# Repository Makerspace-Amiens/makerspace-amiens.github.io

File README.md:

# Makerspace UniLaSalle Amiens

Site vitrine du Makerspace d'UniLaSalle Amiens : <https://makerspace-amiens.fr>

Le site est une page unique et autonome (`index.html`) : toutes les ressources (scripts, modèle 3D, polices) y sont intégrées. Elle est déployée sur GitHub Pages par le workflow `.github/workflows/pages.yml` à chaque push sur `main`.

## Ancien site

L'ancien site Jekyll est archivé :

- branche [`archive`](../../tree/archive)
- tag `site-v1-archive`

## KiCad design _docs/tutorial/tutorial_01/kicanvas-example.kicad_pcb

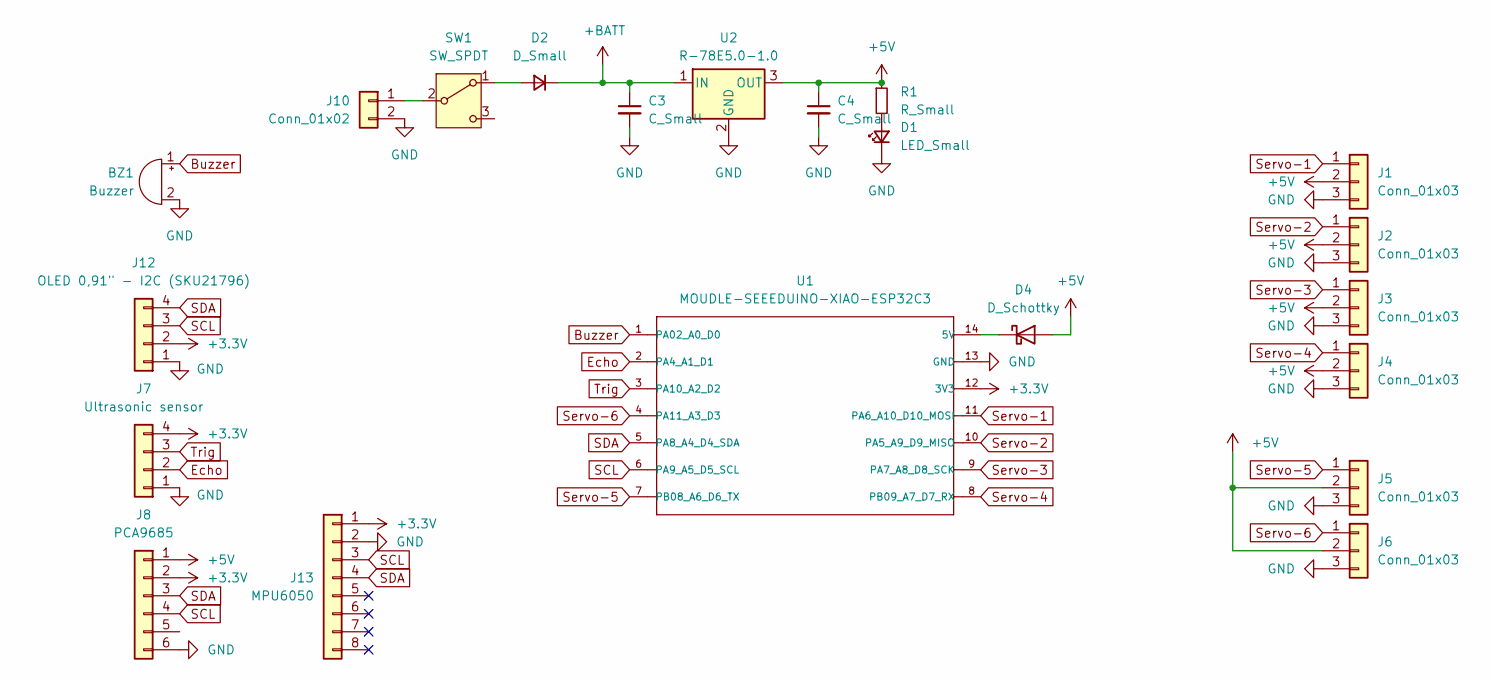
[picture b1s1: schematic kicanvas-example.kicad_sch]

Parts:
BZ1: Buzzer; Buzzer_12x9.5RM7.6
C3, C4: C_Small; C_Disc_D6.0mm_W2.5mm_P5.00mm
D1: LED_Small; LED_D5.0mm
D2: D_Small; D_A-405_P7.62mm_Horizontal
D4: D_Schottky; D_A-405_P7.62mm_Horizontal
J1, J2, J3, J4, J5, J6: Conn_01x03; PinHeader_1x03_P2.54mm_Vertical
J7: Ultrasonic sensor; PinSocket_1x04_P2.54mm_Vertical
J8: PCA9685; PinSocket_1x06_P2.54mm_Vertical
J10: Conn_01x02; Molex_KK-254_AE-6410-02A_1x02_P2.54mm_Vertical
J12: OLED 0,91" - I2C (SKU21796); PinSocket_1x04_P2.54mm_Vertical
J13: MPU6050; PinSocket_1x08_P2.54mm_Vertical
R1: R_Small; R_Axial_DIN0207_L6.3mm_D2.5mm_P10.16mm_Horizontal
SW1: SW_SPDT; SW_100SP1T1B4M2QE
U1: MOUDLE-SEEEDUINO-XIAO-ESP32C3; MOUDLE14P-SMD-2.54-21X17.8MM
U2: R-78E5.0-1.0; Converter_DCDC_RECOM_R-78E-0.5_THT

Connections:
+3.3V: J7.4, J8.2, J12.2, J13.1, U1.12 (3V3)
+5V: C4.1, D4.2 (A), J1.2, J2.2, J3.2, J4.2, J5.2, J6.2, J8.1, R1.1, U2.3 (OUT)
+BATT: C3.1, D2.1 (K), U2.1 (IN)
Buzzer: BZ1.1 (+), U1.1 (PA02_A0_D0)
EN-Driver: J6.1, U1.4 (PA11_A3_D3)
Echo: J7.2, U1.2 (PA4_A1_D1)
GND: BZ1.2 (-), C3.2, C4.2, D1.1 (K), J1.3, J2.3, J3.3, J4.3, J5.3, J6.3, J7.1, J8.6, J10.2, J12.1, J13.2, U1.13 (GND), U2.2 (GND)
unnamed: D1.2 (A), R1.2
unnamed: D2.2 (A), SW1.1 (A)
unnamed: D4.1 (K), U1.14 (5V)
unnamed: J10.1, SW1.2 (B)
SCL: J8.4, J12.3, J13.3, U1.6 (PA9_A5_D5_SCL)
SDA: J8.3, J12.4, J13.4, U1.5 (PA8_A4_D4_SDA)
Servo-1: J1.1, U1.11 (PA6_A10_D10_MOSI)
Servo-2: J2.1, U1.10 (PA5_A9_D9_MISO)
Servo-3: J3.1, U1.9 (PA7_A8_D8_SCK)
Servo-4: J4.1, U1.8 (PB09_A7_D7_RX)
Servo-5: J5.1, U1.7 (PB08_A6_D6_TX)
Trig: J7.3, U1.3 (PA10_A2_D2)

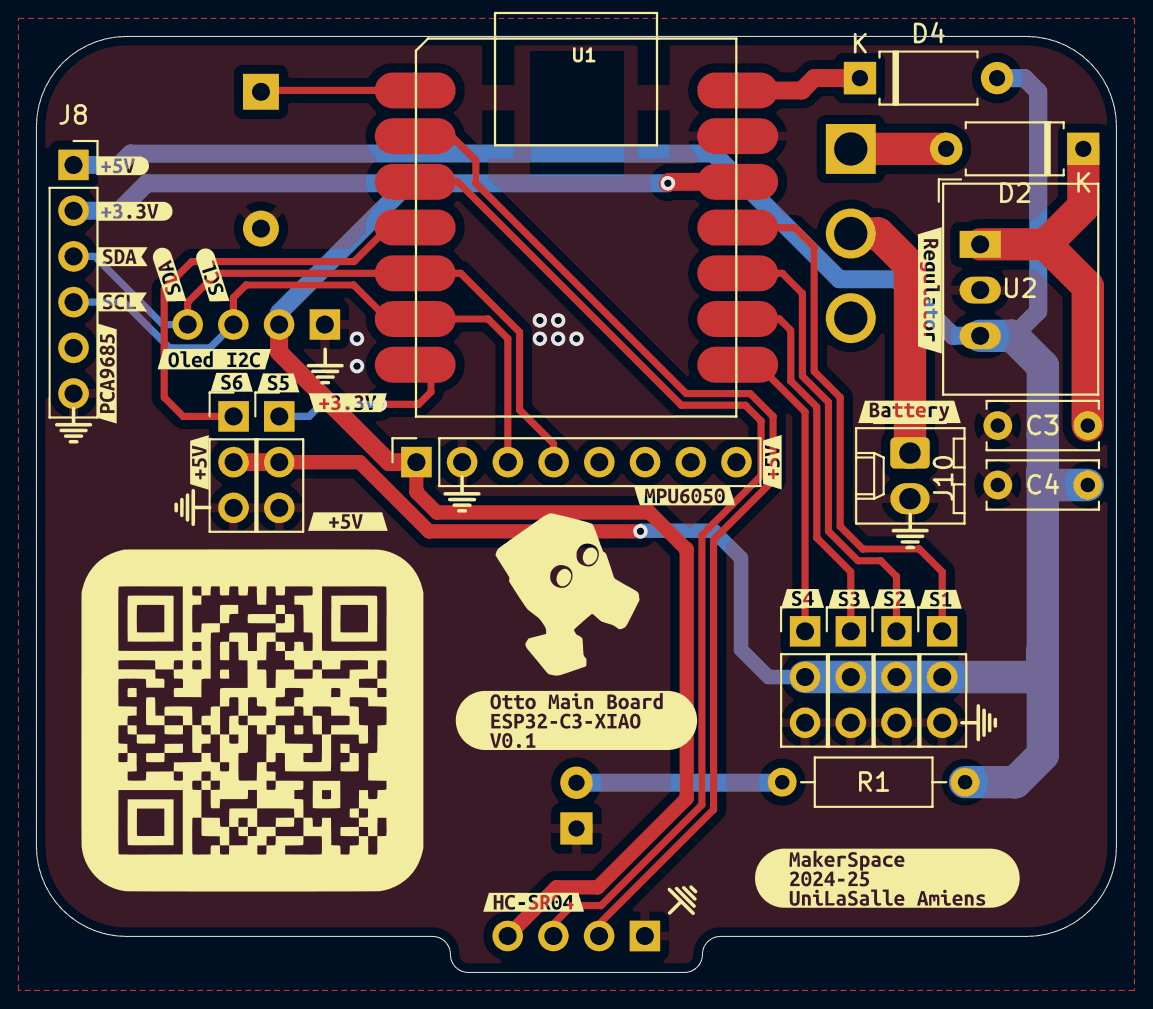
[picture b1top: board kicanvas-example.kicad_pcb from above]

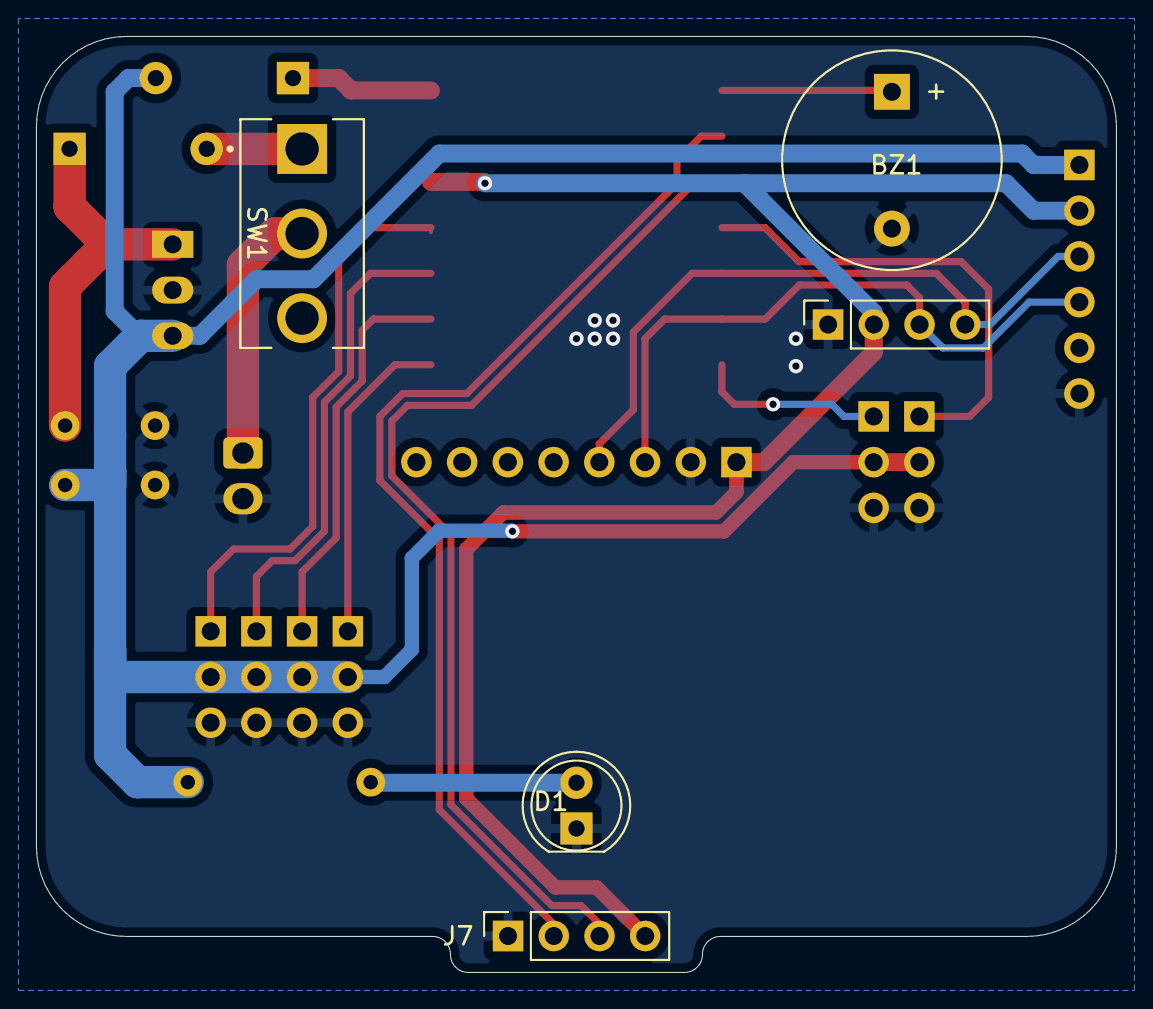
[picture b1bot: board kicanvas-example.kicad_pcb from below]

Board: 2 copper layers, 60.0 x 52.0 mm, 45 parts (5 on the bottom side), 19 nets.

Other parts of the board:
kibuzzard-66E45A06: G***; kibuzzard-66E45A06
kibuzzard-66E45A30: G***; kibuzzard-66E45A30
kibuzzard-66E45AAF: G***; kibuzzard-66E45AAF
kibuzzard-66E45B4D: G***; kibuzzard-66E45B4D
kibuzzard-66E45B8A: G***; kibuzzard-66E45B8A
kibuzzard-66E45B15, kibuzzard-66E45B15#2: G***; kibuzzard-66E45B15
kibuzzard-66E45B34: G***; kibuzzard-66E45B34
kibuzzard-66E45B47: G***; kibuzzard-66E45B47
kibuzzard-66E45B51: G***; kibuzzard-66E45B51
kibuzzard-66E45B85: G***; kibuzzard-66E45B85
kibuzzard-66E45BAB: G***; kibuzzard-66E45BAB
kibuzzard-66E45BBF: G***; kibuzzard-66E45BBF
kibuzzard-66E45BE1: G***; kibuzzard-66E45BE1
kibuzzard-66E45BF0: G***; kibuzzard-66E45BF0
kibuzzard-66E45C9B: G***; kibuzzard-66E45C9B
kibuzzard-66E45C62: G***; kibuzzard-66E45C62
kibuzzard-66E460A4: G***; kibuzzard-66E460A4
kibuzzard-66E460BA: G***; kibuzzard-66E460BA
kibuzzard-66E460D9: G***; kibuzzard-66E460D9
kibuzzard-66E46157: G***; kibuzzard-66E46157
kibuzzard-6707C6B3: G***; kibuzzard-6707C6B3
kibuzzard-6707CF99: G***; kibuzzard-6707CF99
kibuzzard-6707CFA2: G***; kibuzzard-6707CFA2

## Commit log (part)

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2024-01-08 comment remote_include
2024-01-08 add jekyll.yml
2024-01-08 del jekyll.yml
2024-01-08 change parameters
2024-01-08 change ruby and bundler versions
2024-01-08 add bundle install
2024-01-08 change build way
2024-01-10 update link
2024-01-10 new project
2024-01-10 fix typo
2024-01-15 add learn git
2024-01-23 add kicad install tutorial
2024-01-24 Add docs
2024-01-28 cleanup menus
2024-02-20 update gems
2024-02-20 add 3d print tutorials
2024-03-08 integration des projets GEB
2024-03-08 add GEB project and 3D maps
2024-03-15 add RPM visualizer
2024-03-22 add hotspot image
2024-04-05 add 3D files
2024-04-05 fix glb name in layouts
2024-04-12 update ModelViewer3D
2024-04-12 update navigation
2024-04-12 fix navigation
2024-05-22 update projects I3
2024-05-22 update and add projects
2024-05-23 update date
2024-05-24 Update page GEB
2024-05-27 new images for projets
2024-05-27 update photo
2024-05-28 update image
2024-05-28 add robotic section
2024-05-28 add robotic project I1 et I4
2024-05-28 update list project
2024-06-03 generate page for Project I2
2024-06-03 test linkpreview
2024-06-03 add I2 projects with linkpreview
2024-06-07 add guide écologiques
2024-08-27 update minor info
2024-08-27 Add info on how to install correctly a Codspace envirronement
2024-08-27 change numerotation
2024-08-29 change to printables
2024-08-29 add https
2024-09-06 Change tutorials for 3D print - Extract from CAO
2024-09-06 new tutorials Onshape Laser
2024-09-12 add end of the tutorial
2024-09-20 nouveau tutoriel assemblage
2024-09-20 fix ortho
2024-09-30 fix dimensions
2024-10-03 new tutorial - Refill 3D spool
2024-10-15 Added "Tuto Impression 3D avec OrcaSlicer" (WIP 50%), renamed change-bobine to refill-bobine and did minor adjustements
2024-10-23 Kept working on tuto mprimer une pièce
2024-10-24 Completed tuto imprimer une pièce
2024-10-24 Changed Hero Image and added a conclusion
2024-10-24 Changed background of last step
2024-10-25 New tutorial and spelling correction
2024-10-28 Tuto Laser
2024-10-29 Check spelling
2024-10-29 completed tutorial
2024-10-29 Corrections on tuto
2024-11-05 fix name for qrcode
2024-11-05 fix name
2024-11-25 new project page I1
2024-12-04 change url unilasalle amiens
2025-01-21 new way to show external-tools
2025-01-21 New lab content
2025-01-29 add 2025 project
2025-01-30 add projects
2025-01-31 fix images
2025-01-31 add project
2025-02-01 add video
2025-02-03 add content
2025-04-11 clean-up old site
2025-04-11 integrate clean Craft-the-docs versions
2025-04-30 new page - Project day
2025-04-30 add entrepreneuriat
2025-05-20 add project 2025
2025-08-20 integrate docs from previous sites
2025-09-25 Add actual content + chatbot
2025-09-29 add insctructions
2025-09-29 change for compatibility
2025-09-29 gestion des types, ajout des index de collections, ajout de ressources
2025-09-29 bye bye ottonio :( Limit reach
2025-10-09 new part list
2025-10-09 include for part list
2025-10-09 revert list plan -> Waiting new site
2025-10-09 fix collections - add content plan list
2025-10-15 add workshops collection
2025-10-15 add machines
2025-10-20 WIP - workshop one page
2025-10-20 WIP - new card collections filters and items
2025-10-21 add medieval challenge
2025-10-21 add emoji
2025-10-21 WIP - Workshop
2025-10-22 WIP - graph 3D
2025-10-22 Fix link for Medieval Challenge in navigation
    Updated link for '🏰 Medieval Challenge' to point to the correct URL.
2025-10-22 graph 3D integration
2025-10-22 add skill radar
2025-10-24 Wip - Creating spaces
2025-11-03 add content 3d printing ressources
2025-12-04 Added space bar tip
2025-12-08 Fixed typo
2026-01-22 Add Otto-Nio callout to home_callouts.yml
2026-01-22 Update call to action name for Otto-Nio
2026-02-03 Moved Cura tutorial to archive
2026-02-03 Add link to Puzzle Bot documentation
2026-04-07 Add link preview for MIT courses
    Added a new link preview for MIT courses
2026-04-07 BumpMesh to external tools
2026-04-21 Updated Journée des projets
2026-05-12 add video 2025
